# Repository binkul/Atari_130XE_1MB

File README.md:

# Atari 130XE with 1MB simm expansion

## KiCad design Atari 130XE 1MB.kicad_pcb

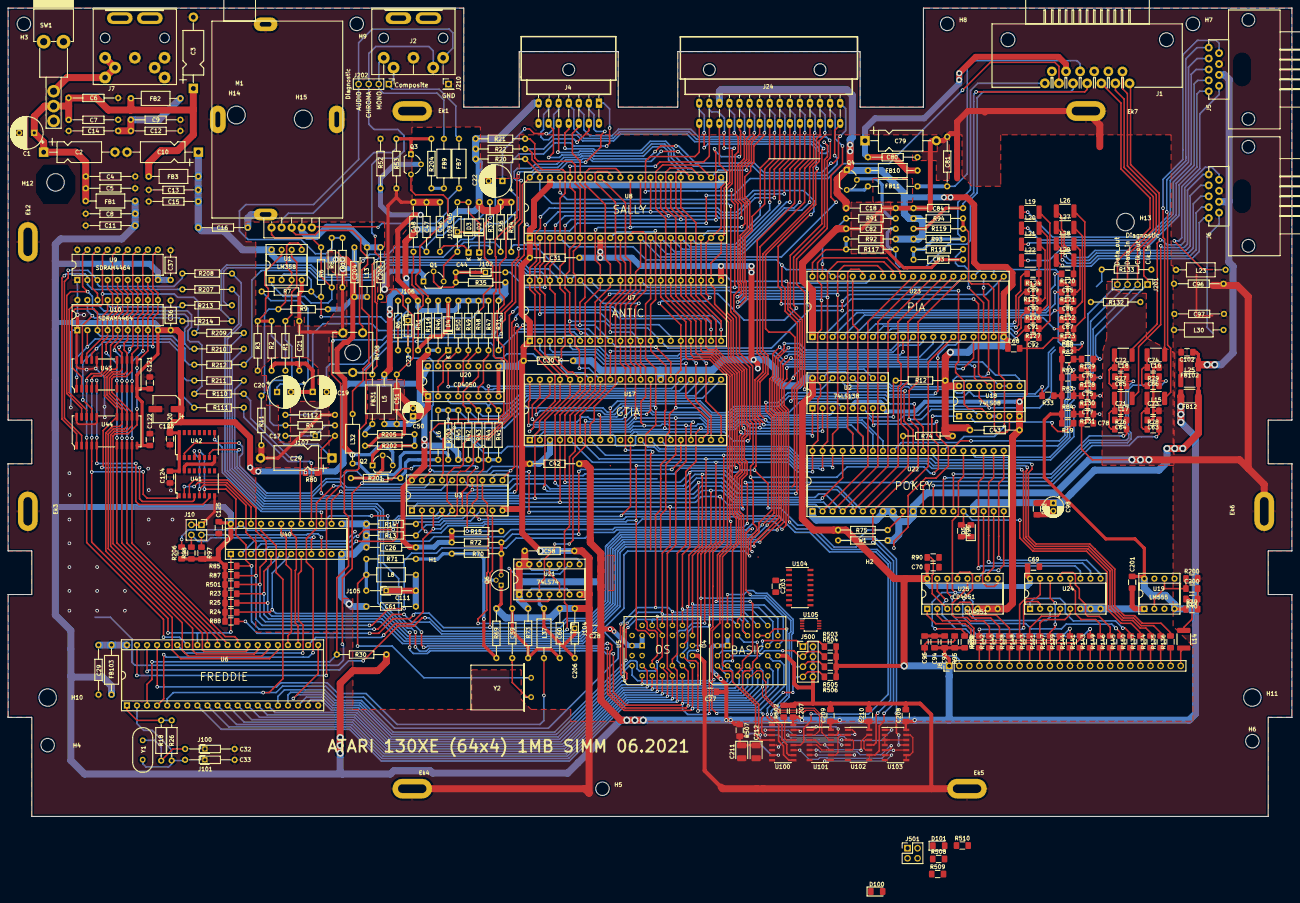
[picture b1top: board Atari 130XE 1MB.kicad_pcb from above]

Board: 2 copper layers, 324.0 x 204.0 mm, 369 parts (0 on the bottom side), 319 nets.

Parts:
C1: 470uF; CP_Radial_D8.0mm_P3.80mm
C2, C3, C10, C79: 22uF; CP_Axial_L11.0mm_D5.0mm_P18.00mm_Horizontal
C4, C13, C18, C26, C29, C30, C31, C42, C43, C48, C51, C58, C61, C204, C205: 100nF; C_Axial_L5.1mm_D2.5mm_P12.50mm_Horizontal
C5, C6, C8, C9, C12, C14, C15, C16, C21, C46, C47, C80, C81, C82, C83, C84, C96, C97, C112: 1nF; C_Axial_L5.1mm_D2.5mm_P12.50mm_Horizontal
C7, C11: 10nF; C_Axial_L5.1mm_D2.5mm_P12.50mm_Horizontal
C17, C23: 47nF; C_Axial_L5.1mm_D2.5mm_P12.50mm_Horizontal
C19, C20, C22: 4,7uF; CP_Radial_D8.0mm_P3.50mm
C24: 10uF; CP_Axial_L11.0mm_D6.0mm_P18.00mm_Horizontal
C27, C28, C68, C69, C70, C93, C120, C121, C122, C124, C125, C200, C201, C207, C208, C209, C210: 100nF; C_1206_3216Metric_Pad1.42x1.75mm_HandSolder
C32, C33, C59, C206: 22pF; C_Axial_L5.1mm_D2.5mm_P12.50mm_Horizontal
C36, C37: 100nF; C_Axial_L3.8mm_D2.6mm_P7.50mm_Horizontal
C44: 68pF; C_Axial_L5.1mm_D2.5mm_P12.50mm_Horizontal
C45: 220pF; C_Axial_L5.1mm_D2.5mm_P12.50mm_Horizontal
C50, C98: 10uF; CP_Radial_D5.0mm_P2.00mm
C60: 560pF; C_Axial_L5.1mm_D2.5mm_P12.50mm_Horizontal
C62, C71, C72, C73, C74, C75, C76, C77, C78, C85, C86, C87, C88, C89, C90, C91, C92, C102: 1nF; C_1206_3216Metric_Pad1.42x1.75mm_HandSolder
C63, C64, C65, C66: 47nF; C_1206_3216Metric_Pad1.42x1.75mm_HandSolder
C94, C95: 10nF; C_1206_3216Metric_Pad1.42x1.75mm_HandSolder
C111: 820pF; C_Axial_L5.1mm_D2.5mm_P12.50mm_Horizontal
C123: 100uF; CP_Elec_6.3x9.9
C203: 1uF; C_1206_3216Metric_Pad1.42x1.75mm_HandSolder
C211: 22uF; CP_EIA-3528-21_Kemet-B_Pad1.50x2.35mm_HandSolder
C212: 4u7; CP_EIA-3528-21_Kemet-B_Pad1.50x2.35mm_HandSolder
D2, D3, D4: 1N4148; D_DO-35_SOD27_P12.70mm_Horizontal
D5, D100, D101: 1N4148; D_1206_3216Metric_Pad1.42x1.75mm_HandSolder
Ek1, Ek2, Ek3, Ek4, Ek5, Ek6, Ek7: Ekran_hole; Ekran_GND
FB1, FB2, FB3, FB7, FB9, FB10, FB11, FB31, FB103: Ferrite_Bead; L_Axial_L7.0mm_D3.3mm_P12.50mm_Horizontal_Fastron_MICC
FB12, FB102: Ferrite_Bead; L_1812_4532Metric_Pad1.30x3.40mm_HandSolder
H1, H2: Hole; Medium_hole
H3, H4, H5, H6, H7, H8, H9: Hole; Hole_3.4mm
H10, H11, H12, H13: Hole; Hole_4.4mm
H14, H15: Hole; MountingHole_4.5mm
J1: SIO; SIO_Slot
J2: Video; DIN_5_pin
J4: Expansion; Expansion_Slot
J5, J6: Joystick_Port; Joystick_Pport
J7: Power; DIN_7_pin
J8: Keyboard; PinHeader_1x24_P2.54mm_Vertical
J10: Mem_on_off; PinHeader_2x02_P2.54mm_Vertical
J24: Cartridge; Cartridge_Slot
J100, J101: cond; PinHeader_1x01_P2.00mm_Vertical
J102, J103, J104, J105, J106, J107: pin; PinHeader_1x01_P2.00mm_Vertical
J201: Diagnostic; PinHeader_1x04_P2.54mm_Vertical
J202: Diag; PinHeader_1x04_P2.54mm_Vertical
J210: Diag; PinHeader_1x01_P2.54mm_Vertical
J500: Basic_sel; PinHeader_2x04_P2.54mm_Vertical
J501: TPP_sel; PinHeader_2x02_P2.54mm_Vertical
L5, L13: 820uH; L_Axial_L7.0mm_D3.3mm_P12.50mm_Horizontal_Fastron_MICC
L6, L23, L30, L32: 100uH; L_Axial_L7.0mm_D3.3mm_P12.50mm_Horizontal_Fastron_MICC
L8: 1,5uH; L_Axial_L7.0mm_D3.3mm_P12.50mm_Horizontal_Fastron_MICC
L14: 22uH; L_1812_4532Metric_Pad1.30x3.40mm_HandSolder
L15, L16, L17, L18, L19, L20, L21, L22, L25, L26, L27, L28, L29: 10uH; L_1812_4532Metric_Pad1.30x3.40mm_HandSolder
L37: Bead or 470R; L_Axial_L7.0mm_D3.3mm_P12.50mm_Horizontal_Fastron_MICC
M1: Modulator; Modulator_TV
Q1, Q2, Q3: 2N3904; TO-92L_Wide
Q4: 2N3906; TO-92_Wide
Q6: 2N3904; TO-92
R1, R11: 2k2; R_Axial_DIN0207_L3.6mm_D2.2mm_P10.16mm_Horizontal
R2, R10, R13, R14, R37, R41, R42, R43, R44, R45, R72: 1k; R_Axial_DIN0207_L3.6mm_D2.2mm_P10.16mm_Horizontal
R3: 6k2; R_Axial_DIN0207_L3.6mm_D2.2mm_P10.16mm_Horizontal
R4: 56k; R_Axial_DIN0207_L3.6mm_D2.2mm_P10.16mm_Horizontal
R5: 470k; R_Axial_DIN0207_L3.6mm_D2.2mm_P10.16mm_Horizontal
R6: 68k; R_Axial_DIN0207_L3.6mm_D2.2mm_P10.16mm_Horizontal
R7, R52: 2k; R_Axial_DIN0207_L3.6mm_D2.2mm_P10.16mm_Horizontal
R8: 5k1; R_Axial_DIN0207_L3.6mm_D2.2mm_P10.16mm_Horizontal
R9, R203: 3k3; R_Axial_DIN0207_L3.6mm_D2.2mm_P10.16mm_Horizontal
R12, R15, R20, R21, R22, R30, R31, R34, R74, R75: 3k; R_Axial_DIN0207_L3.6mm_D2.2mm_P10.16mm_Horizontal
R18: 240; R_Axial_DIN0207_L6.3mm_D2.5mm_P10.16mm_Horizontal
R19, R23, R24, R25, R33, R85, R86, R87, R88, R501: 3k; R_1206_3216Metric_Pad1.42x1.75mm_HandSolder
R26: 1M; R_Axial_DIN0207_L6.3mm_D2.5mm_P10.16mm_Horizontal
R35: 33k; R_Axial_DIN0207_L3.6mm_D2.2mm_P10.16mm_Horizontal
R36: 680; R_Axial_DIN0207_L3.6mm_D2.2mm_P10.16mm_Horizontal
R39: 56k; R_1206_3216Metric_Pad1.42x1.75mm_HandSolder
R40, R90, R128, R129, R130, R131: 100; R_1206_3216Metric_Pad1.42x1.75mm_HandSolder
R46: 1k6; R_Axial_DIN0207_L3.6mm_D2.2mm_P10.16mm_Horizontal
R47: 36k; R_Axial_DIN0207_L3.6mm_D2.2mm_P10.16mm_Horizontal
R48: 18k; R_Axial_DIN0207_L3.6mm_D2.2mm_P10.16mm_Horizontal
R49: 9k1; R_Axial_DIN0207_L3.6mm_D2.2mm_P10.16mm_Horizontal
R50, R73, R92, R93, R94: 4k7; R_Axial_DIN0207_L3.6mm_D2.2mm_P10.16mm_Horizontal
R51: 750; R_Axial_DIN0207_L3.6mm_D2.2mm_P10.16mm_Horizontal
R53, R117, R119: 100; R_Axial_DIN0207_L3.6mm_D2.2mm_P10.16mm_Horizontal
R69, R201: 6k8; R_Axial_DIN0207_L3.6mm_D2.2mm_P10.16mm_Horizontal
R70: 10k; R_Axial_DIN0207_L3.6mm_D2.2mm_P10.16mm_Horizontal
R71: 470; R_Axial_DIN0207_L3.6mm_D2.2mm_P10.16mm_Horizontal
R76, R77, R78, R79: 1k8; R_1206_3216Metric_Pad1.42x1.75mm_HandSolder
R80, R95, R502: 1k; R_1206_3216Metric_Pad1.42x1.75mm_HandSolder
R81, R82, R83, R84, R508, R509: 4k7; R_1206_3216Metric_Pad1.42x1.75mm_HandSolder
R89, R96: 47k; R_1206_3216Metric_Pad1.42x1.75mm_HandSolder
R91: 2k7; R_Axial_DIN0207_L3.6mm_D2.2mm_P10.16mm_Horizontal
R97, R98, R503, R504, R505, R506, R510: 10k; R_1206_3216Metric_Pad1.42x1.75mm_HandSolder
R110, R111, R207, R208, R209, R210, R211, R212, R213, R214: 33; R_Axial_DIN0207_L3.6mm_D2.2mm_P10.16mm_Horizontal
R116: 51; R_Axial_DIN0207_L3.6mm_D2.2mm_P10.16mm_Horizontal
R118, R132, R133: 220; R_Axial_DIN0207_L3.6mm_D2.2mm_P10.16mm_Horizontal
R120, R121, R122, R123, R124, R125, R126, R127, R138, R139, R140, R141, R142, R143, R144, R145, R146, R147, R148, R149, R150, R151, R152, R153: 220; R_1206_3216Metric_Pad1.42x1.75mm_HandSolder
R134, R135, R136: 470; R_1206_3216Metric_Pad1.42x1.75mm_HandSolder
R137: 270; R_1206_3216Metric_Pad1.42x1.75mm_HandSolder
R200: 470k; R_1206_3216Metric_Pad1.42x1.75mm_HandSolder
R202: 180; R_Axial_DIN0207_L3.6mm_D2.2mm_P10.16mm_Horizontal
R204: 47; R_Axial_DIN0207_L3.6mm_D2.2mm_P10.16mm_Horizontal
R205: 150; R_Axial_DIN0207_L3.6mm_D2.2mm_P10.16mm_Horizontal
R206: 3k3; R_1206_3216Metric_Pad1.42x1.75mm_HandSolder
R507: 1k2; R_1206_3216Metric_Pad1.42x1.75mm_HandSolder
RV38: 500k; Potentiometer_ACP_CA9-V10_Vertical_Hole
SW1: Switch_power_on; Switch_ON-OFF
U1: LM358; DIP-8_W7.62mm_Socket
U2: 74LS138; DIP-16_W7.62mm_Socket
U3: MMU; DIP-20_W7.62mm_Socket
U4, U5: 27C010; PLCC-32_THT-Socket
U6: Freddie; DIP-40_W15.24mm_Socket
U7: Antic; DIP-40_W15.24mm_Socket
U8: Sally; DIP-40_W15.24mm_Socket
U9, U10: DRAM_4464; DIP-18_W7.62mm
U17: GTIA; DIP-40_W15.24mm_Socket
U18: 74LS08; DIP-14_W7.62mm_Socket
U19: LM555; DIP-8_W7.62mm_Socket
U20: 4050; DIP-16_W7.62mm_Socket
U21: 74LS74; DIP-14_W7.62mm_Socket
U22: POKEY; DIP-40_W15.24mm_Socket
U23: PIA; DIP-40_W15.24mm_Socket
U24, U25: CD4051B; DIP-16_W7.62mm_Socket
U40: GAL20V8_DIP; DIP-24_W7.62mm_Socket
U41: 74LS157; SOP-16_4.4x10.4mm_P1.27mm
U42: 74LS175; SOP-16_4.4x10.4mm_P1.27mm
U43, U44: DRAM_1MB_4bit; SOJ-26
U100, U104: 74LS157; SOIC-16_3.9x9.9mm_P1.27mm
U101: 74LS74; SOIC-14_3.9x8.7mm_P1.27mm
U102, U103: 74HC02; SOIC-14_3.9x8.7mm_P1.27mm
U105: 74LVC2G74; TSSOP-8_3x3mm_P0.65mm
W1: 0; R_Axial_DIN0207_L3.6mm_D2.2mm_P10.16mm_Horizontal
Y1: Crystal; Crystal_HC18-U_Vertical
Y2: 4,43 MHz; Crystal_HC18-U_Horizontal

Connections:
+5C: C10.1, C13.1, C15.1, C16.2, C204.2, FB3.1, L13.2, Q2.3, R9.1, U1.8
+5P: C62.1, C98.1, FB12.1, L25.2, U22.17
+5V: C9.1, C12.1, C14.1, FB2.1
+5VA: C8.1, C11.1, C18.1, C26.1, C27.1, C28.1, C30.1, C31.1, C36.1, C37.1, C42.1, C43.1, C58.1, C68.1, C69.1, C70.1, C93.1, C94.1, C120.1, C121.1, C122.1, C123.1, C124.1, C125.1, C201.1, C207.1, C208.1, C209.1, C210.1, D2.2, D5.1, D100.1, FB1.1, FB10.2, FB12.2, FB103.1, J4.7, J8.1, J24.13, L5.2, Q4.1, R12.1, R15.1, R19.2, R20.2, R21.1, R22.1, R23.1, R24.1, R25.1, R30.2, R31.1, R33.1, R34.1, R35.1, R36.1, R39.1, R41.1, R42.1, R43.1, R44.1, R45.1, R72.1, R73.1, R74.1, R75.2, R80.2, R81.1, R82.1, R83.1, R84.1, R85.1, R86.1, R87.1, R88.1, R89.2, R92.1, R93.2, R94.2, R95.2, R96.2, R97.1, R98.1, R206.1, R501.1, R503.1, R504.1, R505.1, R506.1, R507.1, R508.1, R509.2, R510.2, U2.16, U3.20, U4.1, U4.31, U4.32, U5.1, U5.31, U5.32, U7.21, U8.8, U9.9, U10.9, U17.27, U18.14, U19.4, U19.8, U21.1, U21.4, U21.10, U21.13, U21.14, U23.20, U24.16, U25.16, U40.24, U41.16, U42.1, U42.16, U43.10, U44.10, U100.16, U101.14, U102.14, U103.14, U104.16, U105.8
A0: J24.5, U4.12, U5.12, U6.8, U7.13, U8.9, U17.2, U22.36, U23.35, U101.2
A1: J24.4, U4.11, U5.11, U6.9, U7.12, U8.10, U17.1, U22.35, U23.36
A2: J24.3, U4.10, U5.10, U6.10, U7.11, U8.11, U17.40, U22.34
A3: J24.2, U4.9, U5.9, U6.11, U7.10, U8.12, U17.39, U22.33, U101.12
A4: J24.C, U4.8, U5.8, U6.12, U7.28, U8.13, U17.38
A5: J24.D, U4.7, U5.7, U6.13, U7.27, U8.14
A6: J24.E, U4.6, U5.6, U6.14, U7.26, U8.15
A7: J24.F, U4.5, U5.5, U6.15, U7.25, U8.16
A8: J24.H, U2.1, U4.27, U5.27, U6.16, U7.24, U8.17
A9: J24.J, U2.2, U4.26, U5.26, U6.17, U7.23, U8.18
A10: J24.P, U2.3, U4.23, U5.23, U6.18, U7.16, U8.19
A11: J24.N, U3.1, U4.25, U5.25, U6.19, U7.22, U8.20
A12: J24.K, U3.2, U5.4, U6.21, U7.17, U8.22, U100.3, U102.3, U102.5
A13: J4.D, U3.3, U5.28, U6.22, U7.18, U8.23
A14: J4.E, U3.4, U7.19, U8.24, U40.3
A14_sel: J500.5, R505.2, U4.29
A15: J4.F, U3.5, U7.20, U8.25, U40.4
A15_sel: J500.3, R504.2, U4.3
A16: U104.14, U105.5
A16_sel: J500.1, R503.2, U4.2
AN0: U7.2, U17.18
AN1: U7.3, U17.19
AN2: U7.5, U17.20
AUDIO: J2.3, J202.4, R8.1, R10.1
BACK0: J6.2, L28.1
BACK1: J5.2, L21.1
BASIC: U3.13, U100.10
BE: U3.18, U42.7
BELL: C23.2, J106.1, U17.15
BO2: J24.S, U7.29, U17.30, U18.3, U22.7, U23.25, U102.8, U102.9
BSC: J8.20, R137.1
CAS: U6.35, U40.8
CASINH: U3.16, U6.4
CASMAN: R110.2, U9.16, U10.16
CCTL: J24.15, U2.10, U102.11
CHROMA: FB31.1, J2.5, J202.3
CLK_IN: C76.1, J1.1, J201.1, R129.1
CLK_OUT: C75.1, J1.2, J201.2, R128.1
COLOR: L32.1, M1.3
COMMAND: C84.1, J1.7, R119.1
COMPOSITE: FB7.2, J2.4, J202.1
D0: J24.10, R207.2, U4.13, U5.13, U7.30, U8.33, U17.7, U22.38, U23.33
D1: J24.9, R208.2, U4.14, U5.14, U7.31, U8.32, U17.6, U22.39, U23.32
D1XX: J4.3, U2.14
D2: J24.8, R209.2, U4.15, U5.15, U7.32, U8.31, U17.5, U22.40, U23.31
D3: J24.L, R210.2, U4.17, U5.17, U7.33, U8.30, U17.4, U22.2, U23.30
D4: J24.6, R211.2, U4.18, U5.18, U7.40, U8.29, U17.37, U22.3, U23.29
D5: J24.7, R212.2, U4.19, U5.19, U7.39, U8.28, U17.36, U22.4, U23.28
D6: J24.11, R213.2, U4.20, U5.20, U7.38, U8.27, U17.35, U22.5, U23.27
D6XX: U2.9, U105.1
D7: J24.M, R214.2, U4.21, U5.21, U7.37, U8.26, U17.34, U22.6, U23.26
DATA_IN: C77.1, J1.3, J201.3, R130.1
DATA_OUT: C78.1, J1.5, J201.4, R131.1
DQ0: R207.1, U9.2, U44.1
DQ1: R208.1, U9.3, U44.2
DQ2: R209.1, U9.15, U44.18
DQ3: R210.1, U9.17, U44.19
DQ4: R211.1, U10.2, U43.1
DQ5: R212.1, U10.3, U43.2
DQ6: R213.1, U10.15, U43.18
DQ7: R214.1, U10.17, U43.19
E3: R12.2, U2.6
EXTAUDIO: C22.1, J4.5
EXTSEL: J4.1, R30.1, U6.3
FA14: U6.23, U40.18
FA15: U6.24, U40.19
FO0: U7.35, U17.29
FWD0: J6.1, L29.1
FWD1: J5.1, L22.1
GND: C1.2, C2.2, C3.2, C4.2, C5.2, C6.2, C7.2, C8.2, C9.2, C10.2, C11.2, C12.2, C13.2, C14.2, C15.2, C16.1, C18.2, C21.1, C24.2, C26.2, C27.2, C28.2, C29.2, C30.2, C31.2, C32.2, C33.2, C36.2, C37.2, C42.2, C43.2, C46.1, C47.1, C48.1, C50.2, C51.2, C58.2, C60.1, C61.1, C62.2, C63.2, C64.2, C65.2, C66.2, C68.2, C69.2, C70.2, C71.2, C72.2, C73.2, C74.2, C75.2, C76.2, C77.2, C78.2, C79.2, C80.2, C81.2, C82.2, C83.2, C84.2, C85.2, C86.2, C87.2, C88.2, C89.2, C90.2, C91.2, C92.2, C93.2, C94.2, C95.2, C96.1, C97.1, C98.2, C102.2, C112.1, C120.2, C121.2, C122.2, C123.2, C124.2, C125.2, C201.2, C203.2, C204.1, C205.2, C206.1, C207.2, C208.2, C209.2, C210.2, C211.2, C212.2, Ek1.1, Ek2.1, Ek3.1, Ek4.1, Ek5.1, Ek6.1, Ek7.1, J1.4, J1.6, J2.2, J4.H, J5.8, J6.8, J7.2, J7.3, J7.5, J7.7, J8.3, J10.1, J10.3, J24.B, J100.1, J101.1, J210.1, J500.2, J500.4, J500.6, J500.8, J501.2, J501.4, M1.6, M1.7, M1.8, M1.9, Q1.1, Q6.1, R3.2, R10.2, R11.2, R13.2, R14.2, R52.2, R53.2, R69.2, R90.2, R200.2, R202.1, R502.2, RV38.1, U1.4, U2.5, U2.8, U3.10, U4.16, U5.16, U6.20, U7.1, U8.1, U8.21, U8.38, U9.1, U9.18, U10.1, U10.18, U17.3, U18.7, U19.1, U20.8, U20.9, U21.7, U22.1, U22.8, U22.9, U22.11, U23.1, U24.6, U24.7, U24.8, U25.6, U25.7, U25.8, U40.12, U40.13, U41.8, U41.15, U42.8, U43.16, U43.20, U44.16, U44.20, U100.6, U100.8, U100.15, U101.7, U102.7, U103.7, U104.2, U104.3, U104.6, U104.8, U104.10, U104.13, U104.15, U105.2, U105.4, W1.2
GTIA: U17.32, U18.8
HALT: J4.C, U7.9, U8.35, U17.26, U40.14
IN0: J8.17, R146.1
IN1: J8.11, R147.1
IN2: J8.8, R148.1
IN3: J8.16, R149.1
IN4: J8.19, R150.1
IN5: J8.10, R151.1
IN6: J8.4, R152.1
IN7: J8.9, R153.1
INTRUPT: C83.1, J1.13, R93.1, R118.1
IRQ: J4.B, R22.2, U8.4, U22.29, U23.37, U23.38
K0: U22.23, U24.11
K1: U22.22, U24.10
K2: U22.21, U24.9
K3: U22.20, U25.11
K4: U22.19, U25.10
K5: U22.18, U25.9
LEFT0: J6.3, L27.1
LEFT1: J5.3, L20.1
LP: R33.2, U7.4, U18.11
MAP: U3.6, U42.2
MONO: FB9.1, J2.1, J202.2
MONO_MOD: M1.4, Q3.1, R53.1, R204.2
MPD: J4.4, R15.2, U3.14
MTR_CLR: C81.1, FB11.1, J1.8
NMI: R21.2, U7.7, U8.6
unnamed: C1.1, C2.1, C3.1, C4.1, C5.1, C6.1, C7.1, FB1.2, FB2.2, FB3.2, SW1.2
unnamed: C17.1, J107.1, R4.2
unnamed: C19.1, C20.2, C21.2, C22.2, R2.1
unnamed: C20.1, R7.2
unnamed: C23.1, R5.1
unnamed: C24.1, R9.2, R11.1, U1.3, U1.5
unnamed: C29.1, FB103.2, U6.40
unnamed: C32.1, R18.2, Y1.1
unnamed: C33.1, R26.2, U6.2, Y1.2
unnamed: C44.1, J102.1, Q1.2, R35.2
unnamed: C45.1, D2.1, D3.2, J103.1
unnamed: C45.2, Q1.3, R36.2
unnamed: C46.2, D3.1, R37.1
unnamed: C47.2, R37.2, RV38.3
unnamed: C48.2, RV38.2, U17.17
unnamed: C50.1, C51.1, L5.1, R46.1, R116.1, U20.1
unnamed: C59.1, C60.2, R73.2, U21.9
unnamed: C59.2, Y2.2
unnamed: C63.1, R78.2, U22.13
unnamed: C64.1, R76.2, U22.15
unnamed: C65.1, R77.2, U22.14
unnamed: C66.1, R79.2, U22.12
unnamed: C71.1, L17.2, R76.1
unnamed: C72.1, L18.2, R77.1
unnamed: C73.1, L15.2, R78.1
unnamed: C74.1, L16.2, R79.1
unnamed: C85.1, L29.2, R120.1
unnamed: C86.1, L28.2, R121.1
unnamed: C87.1, L27.2, R122.1
unnamed: C88.1, L26.2, R123.1
unnamed: C89.1, L22.2, R124.1
unnamed: C90.1, L21.2, R125.1
unnamed: C91.1, L20.2, R126.1
unnamed: C92.1, L19.2, R127.1
unnamed: C95.1, J8.2, R95.1
unnamed: C96.2, L23.2, R133.1
unnamed: C97.2, L30.2, R132.1
unnamed: C102.1, FB102.1, J5.7, J6.7
unnamed: C111.1, L8.1, R71.2, Y2.1
unnamed: C61.2, C111.2, J105.1, L8.2
unnamed: C200.1, R200.1, U19.2, U19.6
unnamed: C200.2, R39.2, R40.1
unnamed: C203.1, D100.2, R508.2, U105.6
unnamed: C206.2, J104.1, L37.1, U17.28, U21.3
unnamed: C211.1, C212.1, R507.2, U101.1, U101.13
unnamed: D4.1, U20.15
unnamed: D4.2, R51.2
unnamed: D5.2, R96.1, R137.2, U22.16
unnamed: D101.1, J501.1, R509.1, U105.7
unnamed: FB7.1, M1.1
unnamed: FB9.2, R204.1
unnamed: FB11.2, Q4.3
unnamed: FB31.2, R205.1
unnamed: FB102.2, L25.1
unnamed: J7.1, J7.4, J7.6, SW1.3
unnamed: J10.2, R97.2, U40.10
unnamed: J10.4, R98.2, U40.9
unnamed: J500.7, R506.2, U100.1
unnamed: J501.3, R510.1, U104.1
unnamed: L6.1, R201.2
unnamed: L6.2, R45.2, R203.2, U17.21
unnamed: L14.1, R40.2
unnamed: L32.2, R203.1
unnamed: M1.5, R6.1, R8.2, U1.1
unnamed: Q2.1, R202.2, R205.2
unnamed: Q2.2, R201.1
unnamed: Q3.2, R46.2, R47.1, R48.1, R49.1, R50.1, R51.1, R52.1
unnamed: Q3.3, R116.2
unnamed: Q4.2, R91.1
unnamed: Q6.2, R69.1, R70.2, R71.1
unnamed: Q6.3, R70.1, R72.2, U17.16
unnamed: R1.1, R4.1, U1.6
unnamed: R1.2, R2.2, R3.1, U1.7
unnamed: R5.2, R6.2, R7.1, U1.2
unnamed: R18.1, R26.1, U6.1
unnamed: R19.1, U18.2
unnamed: R41.2, U17.31, U20.7
unnamed: R42.2, U17.22, U20.11
unnamed: R43.2, U17.23, U20.5
unnamed: R44.2, U17.24, U20.3
unnamed: R47.2, U20.6
unnamed: R48.2, U20.12
unnamed: R49.2, U20.4
unnamed: R50.2, U20.2
unnamed: R74.2, U22.31
unnamed: R75.1, U22.10, W1.1
unnamed: R86.2, U23.22, U23.24
unnamed: R89.1, U22.25, U24.3
unnamed: R90.1, U25.3
unnamed: R91.2, U23.39
unnamed: R110.1, U40.17
unnamed: R111.1, U43.17, U44.17
unnamed: R111.2, U40.16
unnamed: R92.2, R117.2, U23.40
unnamed: R118.2, U23.18
unnamed: R94.1, R119.2, U23.19
unnamed: R120.2, U23.2
unnamed: R121.2, U23.3
unnamed: R122.2, U23.4
unnamed: R123.2, U23.5
unnamed: R124.2, U23.6
unnamed: R125.2, U23.7
unnamed: R126.2, U23.8
unnamed: R127.2, U23.9
unnamed: R81.2, R128.2, U22.27
unnamed: R82.2, R129.2, U22.26
unnamed: R83.2, R130.2, U22.24
unnamed: R84.2, R131.2, U22.28
unnamed: R132.2, U17.8, U18.12
unnamed: R133.2, U17.9, U18.13
unnamed: R134.2, U17.12
unnamed: R135.2, U17.13
unnamed: R136.2, U17.14
unnamed: R138.2, U25.4
unnamed: R139.2, U25.2
unnamed: R140.2, U25.5
unnamed: R141.2, U25.1
unnamed: R142.2, U25.12
unnamed: R143.2, U25.15
unnamed: R144.2, U25.14
unnamed: R145.2, U25.13
unnamed: R146.2, U24.13
unnamed: R147.2, U24.14
unnamed: R148.2, U24.15
unnamed: R149.2, U24.12
unnamed: R150.2, U24.1
unnamed: R151.2, U24.5
unnamed: R152.2, U24.2
unnamed: R153.2, U24.4
unnamed: R502.1, U100.13
unnamed: U2.4, U3.17
unnamed: U17.25, U20.14
unnamed: U7.34, U18.4, U18.5
unnamed: U2.15, U18.9, U18.10
unnamed: U21.2, U21.6
unnamed: U21.5, U21.11
unnamed: U21.8, U21.12
unnamed: U40.15, U42.9
unnamed: U40.22, U41.2
unnamed: U41.4, U43.15, U44.15
unnamed: U41.7, U43.5, U44.5
unnamed: U100.2, U102.1
unnamed: U4.4, U100.4
unnamed: U100.5, U102.4
unnamed: U4.28, U100.7
unnamed: U4.22, U4.24, U100.9
unnamed: U100.11, U103.10
unnamed: U100.14, U103.1
unnamed: U101.5, U103.5
unnamed: U101.6, U102.6
unnamed: U101.8, U103.6
unnamed: U101.9, U102.2
unnamed: U101.4, U101.10
unnamed: U101.3, U101.11, U102.13
unnamed: U102.10, U102.12
unnamed: U103.2, U103.3, U103.4, U103.12
unnamed: U103.8, U103.9, U103.13
unnamed: U5.29, U104.7
unnamed: U5.3, U104.9
unnamed: U5.2, U104.12
O0: U8.37, U18.6
O1: C44.2, U8.3
O2: R20.1, U6.5, U8.39, U18.1, U40.21
OPTION: J8.23, R136.1
OSC: L37.2, U6.37
OUT0: J8.18, R145.1
OUT1: J8.13, R144.1
OUT2: J8.15, R143.1
OUT3: J8.5, R142.1
OUT4: J8.14, R141.1
OUT5: J8.6, R140.1
OUT6: J8.12, R139.1
OUT7: J8.7, R138.1
PB0: R88.2, U3.9, U23.10
PB1: R85.2, U23.11, U41.6, U42.5
PB2: R23.2, U23.12, U40.5, U104.5
PB3: R25.2, U23.13, U40.6, U104.11
PB4: R24.2, U23.14, U40.7
PB5: R206.2, U23.15, U40.23
PB6: R501.2, U23.16, U41.3
PB7: R87.2, U23.17, U41.5, U42.4
PIA: U2.12, U23.23
POKEY: U2.13, U22.30
POT_A0: J6.9, L18.1
POT_A1: J5.9, L16.1
POT_B0: J6.5, L17.1
POT_B1: J5.5, L15.1
PROCEED: C82.1, J1.9, R117.1
RA0: U6.32, U9.14, U10.14, U43.6, U44.6
RA1: U6.31, U9.13, U10.13, U43.7, U44.7
RA2: U6.30, U9.12, U10.12, U43.8, U44.8
RA3: U6.29, U9.11, U10.11, U43.9, U44.9
RA4: U6.28, U9.8, U10.8, U43.11, U44.11
RA5: U6.27, U9.7, U10.7, U43.12, U44.12
RA6: U6.26, U9.6, U10.6, U43.13, U44.13
RA7: U6.25, U9.10, U10.10, U43.14, U44.14
RAS: U6.33, U9.5, U10.5, U40.1, U41.1, U43.4, U44.4
RD4: J24.A, R14.1, U3.7
RD5: J24.14, R13.1, U3.8, U17.11, U100.12
RDY: R34.2, U7.15, U8.2
READY: C79.1, C80.1, FB10.1, J1.10
REF: J4.6, U3.11, U7.8, U40.2
RESET: J8.24, L14.2
RF_VCC: C205.1, L13.1, M1.2
RIGHT0: J6.4, L26.1
RIGHT1: J5.4, L19.1
RNMI: R31.2, U7.6
RST: D101.2, J4.2, U6.39, U7.36, U8.40, U19.3, U23.34
RW: J24.R, U6.38, U7.14, U8.36, U17.33, U22.32, U23.21
S4: J24.1, U3.19
S5: J24.12, U3.12, U103.11
SELECT: J8.22, R135.1
SIOAUDIO: C19.2, C112.2, J1.11
SOUND: C17.2, R80.1, U22.37
START: J8.21, R134.1
TRIG0: J6.6, L30.1
TRIG1: J5.6, L23.1
WRT: U6.34, U9.4, U10.4, U43.3, U44.3

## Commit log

2021-05-03 SIMM update
2021-05-05 Simm finished
2021-05-11 Tracking
2021-05-16 Change THT on SMD
2021-05-23 OSS and Basic in PLCC
2021-05-25 SuperCart
2021-06-03 Add Basci and SO PLCC
2021-07-21 Final modification
2021-08-03 Gerber
